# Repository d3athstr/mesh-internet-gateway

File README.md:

# Mesh Internet Gateway (`meshgw`)

Wired-Ethernet Raspberry Pi + 1 W SX1262 LoRa gateway running **`meshtasticd`**.
Bridges the Empire12 / Techtaria LoRa mesh to the internet over MQTT, and
publishes **E12-owned nodes only** to the public Meshtastic map directories.

PartsBin project **[18]**. Status: **DEPLOYED AND LIVE 2026-09-09.** The HAT is
populated, the Pi is wired and provisioned, and the node is on the mesh with the
MQTT bridge connected.

**The E22 land pattern is VERIFIED.** `meshtasticd` reported `sx1262 init
success` on first start with the module soldered to a rev A board — so the
boards fabbed on the recorded `GEOMETRY_OVERRIDE` are good, and that override is
now cleared in `fab_gate.py`.

**Projected cost ~$81.81**, of which **$35.00 is the Raspberry Pi itself** —
check the shelf first, a spare 3B/3B+/4 makes that line $0. The next largest
is the E22 at **$17.10**, which is what was actually paid on a single-item
AliExpress order; LCSC lists the bare module at ~$7.19, so the difference is
probably bundled shipping and worth checking before buying a second one. The
custom HAT is ~$0.80 ($4 for 5 boards) and the printed enclosure ~$1.20 of
filament — between them under 3 % of the build.

---

## Why this exists

Today the mesh's only internet-adjacent node is the Heltec V4 gateway
`!f66ae684`, a WiFi-attached node on the IoT VLAN. It is a poor
foundation for an internet bridge:

| Problem | Evidence |
|---|---|
| ESP32 **WiFi-hang** — CPU alive, WiFi stack dead, every TCP client drops | Down again **2026-08-10 ~12:37**, ops bridge crash-looping `No route to host` → `BrokenPipe`. Needs a Tuya-switch power cycle to recover. |
| Serves **one** streaming TCP-API client, reliably | Already forced HA onto its own dedicated V3 radio (**D049**) |
| Bridge does **not** auto-reconnect | `meshtastic-bridge-watchdog.timer` exists solely to paper over it |
| WiFi-only | No wired path; it lives on E12-DMZ WiFi |

That radio is on the **load-bearing OOB control path** (4th reach channel,
D048). Hanging an internet/MQTT bridge off it stacks a new dependency on the
component that is already the mesh's most frequent outage.

`meshgw` is a separate, wired, purpose-built box. The V4 keeps doing C&C;
`meshgw` owns the internet bridge.

---

## Design

| Piece | Choice | Why |
|---|---|---|
| Host | **Raspberry Pi 3B/3B+** (wired Ethernet) | Native Ethernet kills the WiFi-hang failure mode. `meshtasticd` is a real Linux daemon — multiple concurrent API clients, no single-TCP-slot contention. Cheapest board with Ethernet + 40-pin header; a spare is likely already on the shelf. |
| Radio | **Ebyte E22-900M30S** (SX1262 + PA, 30 dBm) | ~$14 bare module vs ~$30 for a commercial LoRa HAT, and **1 W / 30 dBm** vs the Heltec's 22 dBm SX1262 ceiling — ~8 dB more link budget on the same mesh. |
| Carrier | **Custom HAT PCB** (`hardware/meshgw-hat/`) | A bare module needs a carrier. KiCad 9 headless, `gen.py` + freerouting — same workflow as the OSL / FD2 / Warden carriers. |
| Enclosure | **3D-printed, parametric** (`enclosure/`) | OpenSCAD source. Indoor shelf/rack box — *not* weatherproof. |
| Uplink | MQTT → `mqtt.meshtastic.org` | What makes nodes appear on the public map directories. |

### Ruled out: ESP32 + Ethernet

WT32-ETH01 (ESP32 + LAN8720) would have been the cheapest wired option
(~$8). **Rejected:** native ESP32 Ethernet support is
[meshtastic/firmware PR #9586](https://github.com/meshtastic/firmware/pull/9586),
which is **closed and never merged** (verified 2026-08-10 via the GitHub API).
Using it means maintaining a firmware fork on the OOB control path. Not
acceptable for this role.

### Ruled out: reuse an in-stock Heltec V4

Zero cost (2 on hand), but it reintroduces the exact WiFi-hang failure mode
that has the current gateway down as this is being written. Reasonable as a
**cold standby**, not as the primary.

---

## Privacy boundary — read `docs/privacy-boundary.md`

This is the part that must not be got wrong.

- **Only E12-owned nodes** are published: `meshgw` itself, the Heltec V4
  gateway, the HA V3, and the e12solar RAK router.
- **Techtaria customer-home endpoints stay dark.** No `ok_to_mqtt`, no map
  reporting, ever. Publishing them would put approximate customer home
  locations on public maps.
- **`paw-cmd` (idx 1, C&C) and `Techtaria` (idx 2, community) have uplink AND
  downlink OFF.** Only the default primary channel uplinks. Downlink on the
  C&C channel would let internet-sourced packets inject into the command path.

The HMAC envelope on the C&C receiver is a second line of defence, not a
reason to relax the first.

---

## Repo layout

```
config/meshtasticd/    config.yaml (E22 pinout), MQTT + channel policy, systemd
hardware/meshgw-hat/   KiCad: netlist.py, gen.py, gen_pcb.py, route.sh,
                       check_geometry.py, lib.pretty/
enclosure/             OpenSCAD parametric case + build notes
docs/                  design notes, privacy boundary, provisioning runbook
scripts/               provisioning helpers
```

`netlist.py` is the **single source of truth for the pinout** — the schematic
generator, the board generator and (by hand) `config/meshtasticd/config.yaml`
all derive from it. It used to be duplicated in `gen.py` and `gen_pcb.py` with
a comment saying the two must mirror each other; on 2026-08-11 they silently
stopped mirroring each other. Change the map in one place.

## The HAT is mechanically verified, the footprints are not

These are two different claims and only the first one is true.

`check_geometry.py` asserts 27 facts about the **routed** board against the
Raspberry Pi HAT mechanical specification and the Pi 3B+: outline 65 x 56 mm
with R3 corners, all 40 header pads on the spec grid from pin 1 at
(8.37, 4.77), four 2.75 mm mounting holes with 6.2 mm isolated lands, no
copper over the Pi 3B+ PoE header, the ground pour actually filled, and the
`+5V` width. It exists because on this toolchain **a board can pass DRC with
0 violations and 0 unconnected and still be scrap** — the previous revision
of this board did exactly that with its two header rows swapped, which would
have put every SPI signal on its neighbour's pin.

Run it on anything you are about to fab. `route.sh` runs it automatically.

Two deliberate deviations from the spec: there are no camera/display flex
cutouts, and there is no ID EEPROM. Without the EEPROM this is a board in the
HAT *form factor*, not a certified HAT, and the Pi will not auto-configure it
— which is fine here, because `meshtasticd` is told the pinout explicitly.

### Pi 3B+ PoE header

The 3B+ adds a 4-pin PoE header (J14) that the 3B does not have, and it stands
tall enough to foul a HAT. The board has an **edge-open notch** rather than an
enclosed cutout, because J14 leaves only ~1 mm to the board edge and an
enclosed cutout would leave a 1 mm FR4 bridge that would snap.

Fit is the smaller reason. J14 sits on the Ethernet magnetics' centre taps, so
on a PoE-capable switch those pins can carry ~48-57 V — and this is by
definition a wired-Ethernet gateway, so it is exactly the machine likely to be
plugged into such a switch. Copper over J14 is checked for, not assumed.

## Build state

| Item | State |
|---|---|
| PartsBin project [18] + BOM | **done** — 11 lines |
| meshtasticd config | **verified on hardware** — SX1262 comes up on the documented pinout |
| Device provisioning script | **run against real hardware 2026-09-09 and fixed** — three defects that aborted it under `set -e` (`position.ok_to_mqtt` is not a field; region/coordinate writes reboot the radio; `mqtt.tls_enabled` is rejected by meshtasticd). Admin key and all channel PSKs come from Vault |
| HAT PCB | **rev A, gerbers built, cleared to order 2026-08-12.** Mechanically verified against the HAT spec and the Pi 3B+ (see below); 119 segments, 0 vias, DRC 0/0, ERC 0, 27/27 mechanical assertions, schematic netlist matches `netlist.py`. Fab package `out/fab/meshgw-hat-revA-gerbers.zip`. **Exported on a recorded override — U1's land pattern still has not met a physical module. CHECK U1'S FIT BEFORE SOLDERING.** See `fab_gate.py` |
| Enclosure | **DRAFT** — all three parts render solid, dimensions not validated against a real Pi + HAT stack. Print `coupon` first |
| Deployment | **LIVE 2026-09-09** — wired primary on `meshgw.empire12.net`, MQTT connected, map reporting on. MQTT is PLAINTEXT: meshtasticd rejects the whole MQTT config when `tls_enabled` is set |

### Bare boards were ordered with U1's land pattern unverified — on purpose

Don's call, 2026-08-12, recorded in `fab_gate.py` rather than laundered into a
flag that claims the unknown was resolved. `GEOMETRY_VERIFIED` is still
`False`; a separate `GEOMETRY_OVERRIDE` string permits the export and says who
decided, when, and why. Six weeks from now "verified" and "we decided to risk
it" are very different things to read.

The reasoning: boards are ~$2 and JLCPCB shipping is $6–25, so batching this
into the same checkout as OSL, FD2, pool and Sentinel costs ~$2 marginal.
Holding it back would pay that shipping charge again later *with certainty*.
If the land pattern is wrong the loss is ~$2 of board plus one respin's
shipping — cheaper in expectation than waiting, unless no further order is
ever placed.

**This is a real risk, not a formality.** The E22 solders to castellated pads,
so a wrong land pattern makes these boards scrap. That is unlike the Sentinel
carrier, where the open items were modules on headers and a wrong guess costs
a module rather than a respin.

**When the module arrives, before any soldering:** offer it up to the bare
board. Check the 2.54 mm pitch, both irregular gaps (7.60 mm pin 19→20,
5.46 mm pin 21→22), and that the castellations land on the 1 mm of pad left
outside the module body. Then set `GEOMETRY_VERIFIED = True` and clear
`GEOMETRY_OVERRIDE`. The board silkscreens the same warning, because that is
the object you will be holding at that moment.

### Still to check before the parts go on

1. **The E22-900M30S land pattern, against the physical module** (above). The
   footprint is internally self-consistent with its cited datasheet figures —
   pad count, first-pad offset, pitch, both irregular gaps and the pin ring
   direction were re-checked 2026-08-12 — but that only proves it was
   transcribed correctly, not that the source figures are right. Note the
   deliberate deviation: the land is 2.0 mm wide against a 0.80 mm
   castellation, centred on the body edge so 1 mm sits outside for a solder
   fillet. That is correct practice; do not "fix" it back to 0.80.
2. **Hand-check power-trace width.** KiCad DRC has no current check. The E22
   pulls ~650 mA peak on a 30 dBm TX burst; `route.sh` asks for 0.4 mm on
   `+5V`, which IPC-2221 puts at ~1.24 A on 1 oz external copper for a 10 °C
   rise — about 1.9x the peak. It is not wider because it cannot be: every
   `+5V` run has to thread the 1.04 mm gaps between the header's pads, and at
   0.5 mm and 1.0 mm freerouting could not finish the board at all. If you
   want more margin, the honest fix is a second `+5V` path on B.Cu, not a
   bigger number in `route.sh`.
3. **Confirm the Pi's 5V rail holds through a TX burst.** The E22 runs from
   **5 V, not 3V3** — the datasheet is explicit that ">=5.0 V ensures output
   power", and its SPI/control pins are 3.3 V logic so they land on the Pi's
   GPIO directly. A sagging rail during TX presents as terrible range, not as
   a power fault, which is why `provision-meshgw.sh` starts at `tx_power 22`
   and leaves 30 for after the rail is proven.
4. Check SMA vs **RP**-SMA on the pigtail against the antennas in stock.
5. **Swap C1 for a 10 V or 16 V part.** The 1000 µF in stock is rated 6.3 V;
   on a 5 V rail that is ~26 % headroom, right at the usual 80 % derating
   limit, and the Pi's 5 V rail does not sit low. The C1 footprint
   (D8.0 mm, P3.50 mm) takes either.
6. **Print the enclosure `coupon`** and offer it up to a real Pi 3B before
   committing to the ~4 h full base print.

> **Never power the E22 without an antenna attached.** 1 W into an open
> circuit damages the PA.

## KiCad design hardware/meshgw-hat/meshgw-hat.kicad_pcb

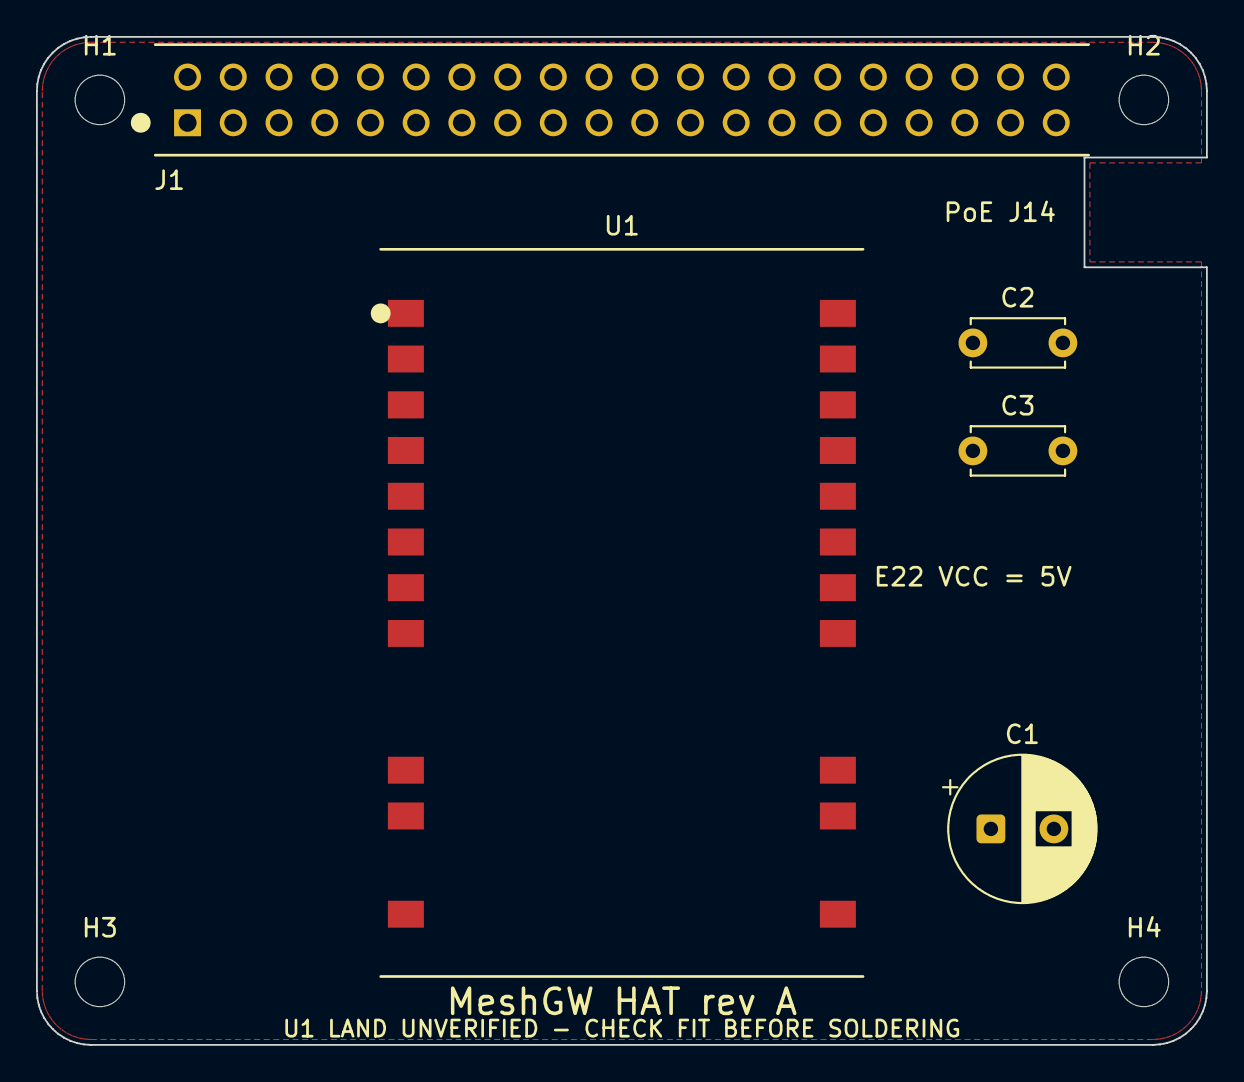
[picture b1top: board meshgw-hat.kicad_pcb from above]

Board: 2 copper layers, 65.0 x 56.0 mm, 9 parts (0 on the bottom side), 12 nets, no tracks yet.

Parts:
C1: CP_Radial_D8.0mm_P3.50mm
C2, C3: C_Disc_D5.0mm_W2.5mm_P5.00mm
H1, H2, H3, H4: MountingHole_2.75mm
J1: RPi_GPIO40; RPi_GPIO40_Horizontal
U1: E22-900M30S; E22_900M30S

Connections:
+3V3: J1.1, J1.17
+5V: C1.1, C2.1, C3.1, J1.2, J1.4, U1.9, U1.10
BUSY: J1.13, U1.14
DIO1: J1.11, U1.13
GND: C1.2, C2.2, C3.2, J1.6, J1.9, J1.14, J1.20, J1.25, J1.30, J1.34, J1.39, U1.1, U1.2, U1.3, U1.4, U1.5, U1.11, U1.12, U1.20, U1.22
MISO: J1.21, U1.16
MOSI: J1.19, U1.17
NRST: J1.15, U1.15
NSS: J1.29, U1.19
RXEN: J1.31, U1.6
SCK: J1.23, U1.18
TXEN: J1.33, U1.7

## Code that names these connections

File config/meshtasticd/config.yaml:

# meshtasticd — Mesh Internet Gateway (meshgw)
# Install to /etc/meshtasticd/config.yaml
#
# This file describes HARDWARE ONLY (which radio, on which pins). Region,
# channels, MQTT and map reporting are *device* settings held in the node's
# own config — see scripts/provision-meshgw.sh, which is the authority for
# those and encodes the privacy boundary.
#
# Pin numbers are BCM GPIO. The authority for this map is
# hardware/meshgw-hat/netlist.py — it is what the copper actually does, and
# this file only tells meshtasticd about it. If they disagree, the radio does
# not come up. The starting point was the open-source MeshAdv-Pi-Hat reference
# design (https://github.com/chrismyers2000/MeshAdv-Pi-Hat) but this HAT
# DIVERGES from it: every control line was moved onto an odd-numbered header
# pin (the Pi's inner row) because the reference map could not be routed on a
# board this size, and because the resulting boot-time pull states are safer —
# GPIO5 idles the chip DESELECTED, where the reference's GPIO21 asserted
# chip-select on every boot. netlist.py has the full reasoning.
#
# UNVERIFIED against real hardware — nothing has been built yet.

Lora:
  Module: sx1262
  # SPI0. Note CS is a plain GPIO (software chip-select), NOT CE0/GPIO8.
  spidev: spidev0.0
  CS: 5            # header pin 29
  IRQ: 17          # header pin 11 — E22 DIO1
  Busy: 27         # header pin 13
  Reset: 22        # header pin 15
  # E22-900M30S has a PA and an RF switch — TXen/RXen are REQUIRED. Omit them
  # and the module transmits into a closed switch: no range, possible damage.
  TXen: 13         # header pin 33
  RXen: 6          # header pin 31
  # The E22's SX1262 clocks from a TCXO fed off DIO3. Without this the radio
  # either fails to start or drifts off frequency.
  DIO3_TCXO_VOLTAGE: true

  # 30 dBm (1 W) is the module's rated ceiling. Leave headroom rather than
  # pinning the maximum until the supply rail is proven under TX burst —
  # brownout during TX looks exactly like a bad antenna.
  # Set the actual value as a device setting (lora.tx_power), not here.

Logging:
  LogLevel: info
  # Journald picks this up; the ops Wazuh agent ships it (see docs/).

Webserver:
  # Local diagnostics only. Do NOT expose this off-box — meshtasticd's
  # webserver is unauthenticated, the same reason the HA TCP-proxy was left
  # off (see meshtastic-lora-ha-node memory).
  Port: 9443
  RootPath: /usr/share/meshtasticd/web

General:
  MaxNodes: 200
  MaxMessageQueue: 100
